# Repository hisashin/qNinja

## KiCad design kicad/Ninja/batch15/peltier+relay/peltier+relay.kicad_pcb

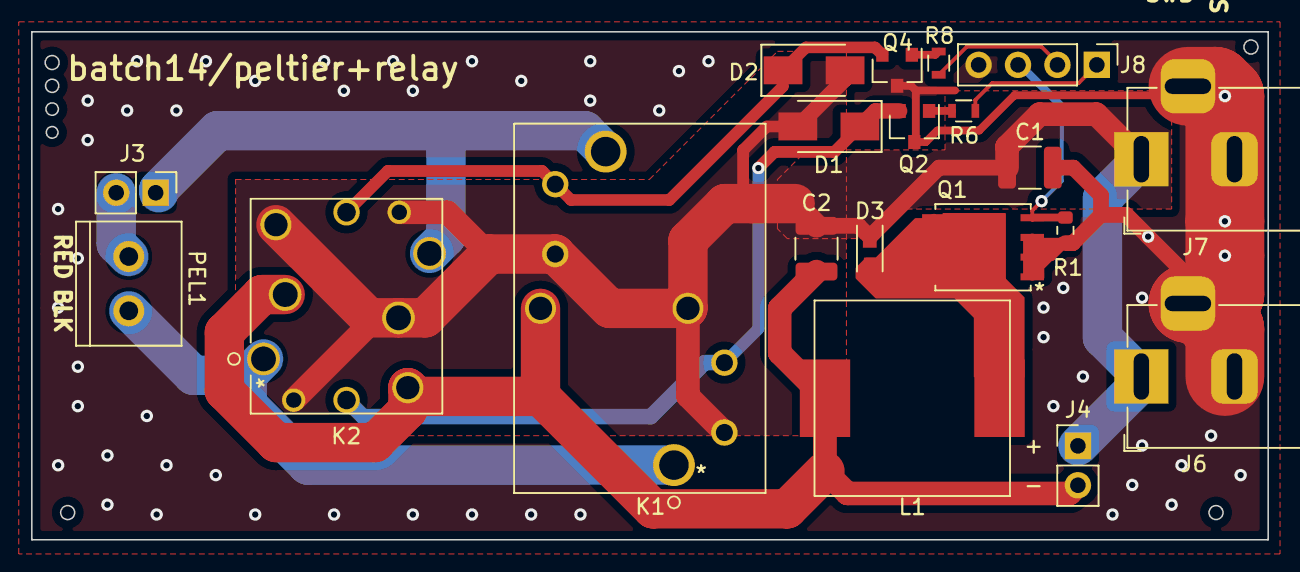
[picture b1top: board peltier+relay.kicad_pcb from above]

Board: 2 copper layers, 79.7 x 32.7 mm, 20 parts (0 on the bottom side), 14 nets.

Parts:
C1, C2: 22uF; C_1210_3225Metric
D1, D2: DIODE; D_SMA
D3: D_Schottky; MSS1P3L-M3&slash_89A
J3, J4: Conn_01x02_Female; Pin_Header_Straight_1x02_Pitch2.54mm
J6, J7: Barrel_Jack_Switch; BarrelJack_Horizontal
J8: Conn_01x03_Male; Pin_Header_Straight_1x04_Pitch2.54mm
K1: EP2-3L3SAb
K2: EX2-2U1S
L1: SRP1265C-220M; SRP1265C
PEL1: Screw_Terminal_01x02; TB_SeeedOPL_320110028
Q1: SIRA88BDP-T1-GE3; PowerPAK_SO-8_Long
Q2, Q4: Q_NPN_BCE; SOT-23
R1: 10k; R_0603_1608Metric
R6, R8: 10k; R_0603

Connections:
12V: C1.1, C2.1, D1.2, D2.2, D3.1, J4.1, J6.1, J7.1, K1.2, K1.4, K1.6, K2.2, K2.5, K2.7, K2.9
/PEL1: D1.1, K1.3, K2.3, Q2.2
/PEL3: D2.1, K1.7, K2.8, Q4.2
/PEL_BLK: K1.1, K2.1, PEL1.2
/PEL_RED: J3.1, K1.8, K2.6
GND: C1.2, J6.2, J6.3, J7.2, J7.3, J8.4, Q1.1, Q1.2, Q1.3, Q2.3, Q4.3, R1.2
unnamed: D3.2, L1.1, Q1.5, Q1.6, Q1.7, Q1.8
unnamed: J3.2, PEL1.1
unnamed: Q2.1, R6.1
unnamed: Q4.1, R8.2
PEL_PWM: J8.3, Q1.4, R1.1
PEL_SWA: J8.1, R6.2
PEL_SWB: J8.2, R8.1
REG_OUT: C2.2, J4.2, K1.5, K2.4, K2.10, L1.2

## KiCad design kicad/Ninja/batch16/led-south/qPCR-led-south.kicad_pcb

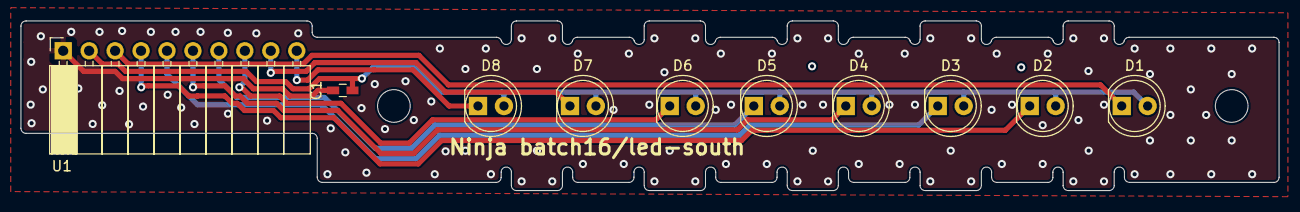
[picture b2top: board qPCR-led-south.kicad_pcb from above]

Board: 2 copper layers, 123.1 x 16.6 mm, 10 parts (0 on the bottom side), 10 nets.

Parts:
C1: C; C_0603_HandSoldering
D1, D2, D3, D4, D5, D6, D7, D8: LED; LED_D5.0mm
U1: Conn_02x05; Socket_Strip_Angled_1x10_Pitch2.54mm

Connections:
GND: C1.2, U1.1
OUT1: D1.1, U1.3
OUT2: D2.1, U1.4
OUT3: D3.1, U1.5
OUT4: D4.1, U1.6
OUT5: D5.1, U1.7
OUT6: D6.1, U1.8
OUT7: D7.1, U1.9
OUT8: D8.1, U1.10
VCC: C1.1, D1.2, D2.2, D3.2, D4.2, D5.2, D6.2, D7.2, D8.2, U1.2

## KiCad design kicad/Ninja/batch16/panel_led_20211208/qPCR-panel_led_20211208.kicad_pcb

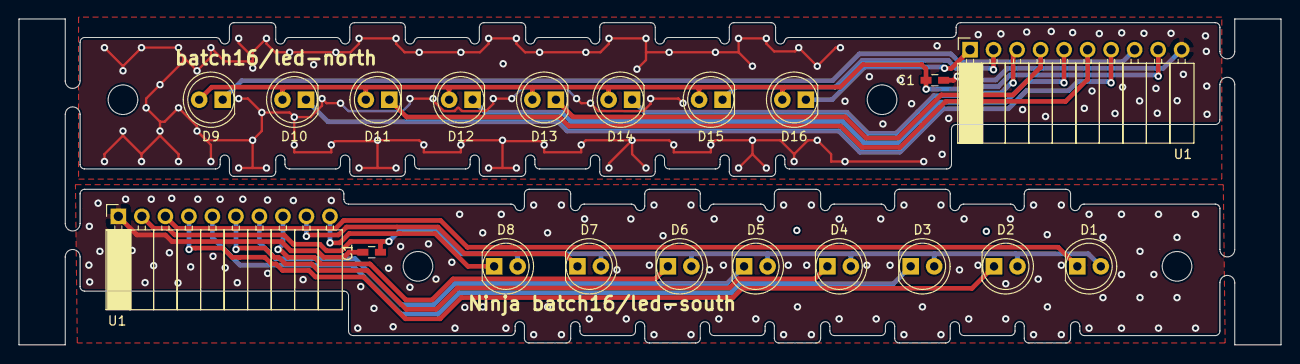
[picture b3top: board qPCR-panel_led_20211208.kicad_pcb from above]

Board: 2 copper layers, 136.3 x 35.2 mm, 20 parts (0 on the bottom side), 18 nets.

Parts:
C1, C1#2: C; C_0603_HandSoldering
D1, D2, D3, D4, D5, D6, D7, D8, D9, D10, D11, D12, D13, D14, D15, D16: LED; LED_D5.0mm
U1, U1#2: Conn_02x05; Socket_Strip_Angled_1x10_Pitch2.54mm

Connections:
GND: C1.2, C1#2.2, U1.10, U1#2.1
OUT1: D1.1, U1#2.3
OUT2: D2.1, U1#2.4
OUT3: D3.1, U1#2.5
OUT4: D4.1, U1#2.6
OUT5: D5.1, U1#2.7
OUT6: D6.1, U1#2.8
OUT7: D7.1, U1#2.9
OUT8: D8.1, U1#2.10
OUT9: D9.1, U1.8
OUT10: D10.1, U1.7
OUT11: D11.1, U1.6
OUT12: D12.1, U1.5
OUT13: D13.1, U1.4
OUT14: D14.1, U1.3
OUT15: D15.1, U1.2
OUT16: D16.1, U1.1
VCC: C1.1, C1#2.1, D1.2, D2.2, D3.2, D4.2, D5.2, D6.2, D7.2, D8.2, D9.2, D10.2, D11.2, D12.2, D13.2, D14.2, D15.2, D16.2, U1.9, U1#2.2

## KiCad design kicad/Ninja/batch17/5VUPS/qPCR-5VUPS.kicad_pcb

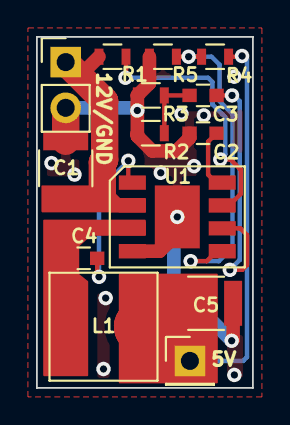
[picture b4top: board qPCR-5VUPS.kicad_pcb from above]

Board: 2 copper layers, 12.0 x 19.5 mm, 14 parts (0 on the bottom side), 10 nets.

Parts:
C1, C5: 22uF; C_1210
C2: 0.1uF; C_0603
C3, C4: 0.01uF; C_0603
J1: Conn_01x02_Male; Pin_Header_Straight_1x02_Pitch2.54mm
J2: Conn_01x01_Male; Pin_Header_Straight_1x01_Pitch2.54mm
L1: 10uH; VLS6045EX-3R3N
R1: 100k/150k; R_0603
R2, R3, R5: 10k; R_0603
R4: 47k; R_0603
U1: AP6503

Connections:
5V_UPS: C5.2, J2.1, L1.1, R4.1
12V_UPS: C1.2, J1.1, R1.1, U1.2
GND: C1.1, C2.1, C5.1, J1.2, R2.2, R3.2, R5.2, U1.4, U1.9
unnamed: C2.2, U1.8
unnamed: C3.1, R2.1, R3.1
unnamed: C3.2, U1.6
unnamed: C4.1, U1.1
unnamed: C4.2, L1.2, U1.3
unnamed: R1.2, U1.7
unnamed: R4.2, R5.1, U1.5

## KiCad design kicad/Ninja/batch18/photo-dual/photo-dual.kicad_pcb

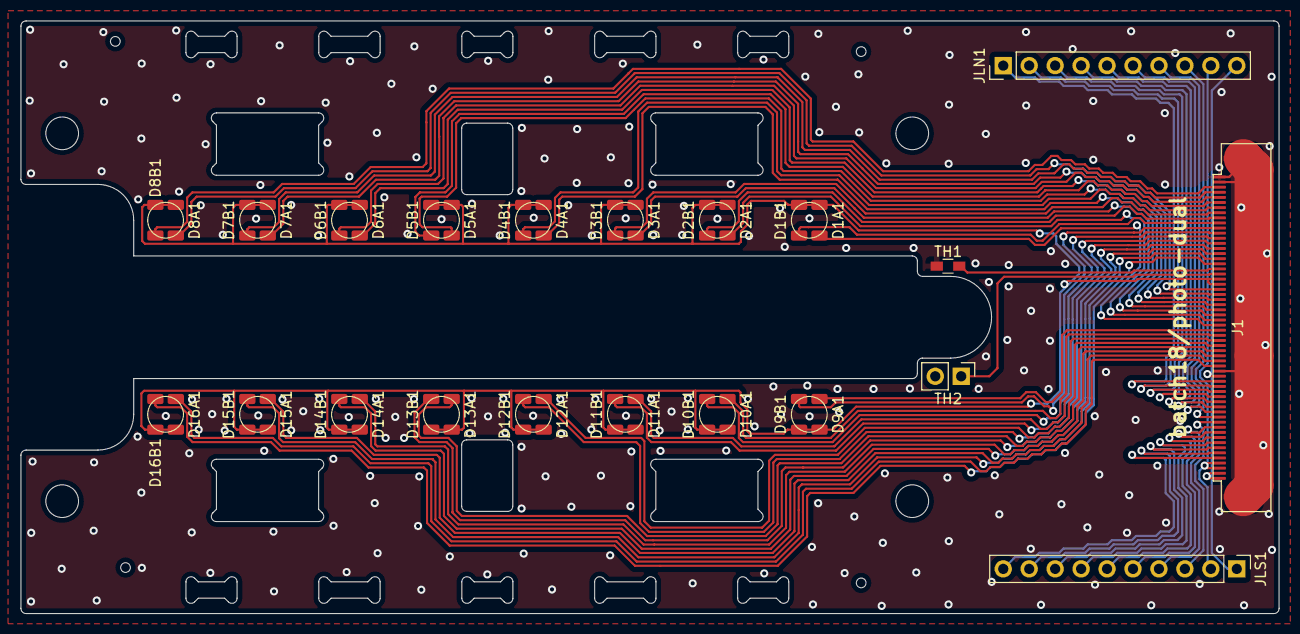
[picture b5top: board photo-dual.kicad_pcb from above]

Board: 2 copper layers, 123.1 x 58.0 mm, 37 parts (0 on the bottom side), 54 nets.

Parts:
D1A1, D1B1, D2A1, D2B1, D3A1, D3B1, D4A1, D4B1, D5A1, D5B1, D6A1, D6B1, D7A1, D7B1, D8A1, D8B1, D9A1, D9B1, D10A1, D10B1, D11A1, D11B1, D12A1, D12B1, D13A1, D13B1, D14A1, D14B1, D15A1, D15B1, D16A1, D16B1: D_Photo; D_1206_nosilk
J1: Conn_01x60_Male; FFC_60_Ali_HUISHUNFA
JLN1: Conn_01x10_Male; Pin_Header_Straight_1x10_Pitch2.54mm
JLS1: Conn_01x10_Male; Pin_Header_Straight_1x10_Pitch2.54mm
TH1: Thermistor; R_0603_HandSoldering
TH2: Thermistor; PinHeader_1x02_P2.54mm_Vertical

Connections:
/N_LED_OUT1: J1.20, JLN1.1
/N_LED_OUT2: J1.19, JLN1.2
/N_LED_OUT3: J1.18, JLN1.3
/N_LED_OUT4: J1.17, JLN1.4
/N_LED_OUT5: J1.16, JLN1.5
/N_LED_OUT6: J1.15, JLN1.6
/N_LED_OUT7: J1.14, JLN1.7
/N_LED_OUT8: J1.13, JLN1.8
/N_PD_OUT1: D1A1.2 (A), J1.31
/N_PD_OUT2: D1B1.2 (A), J1.51
/N_PD_OUT3: D2A1.2 (A), J1.32
/N_PD_OUT4: D2B1.2 (A), J1.52
/N_PD_OUT5: D3A1.2 (A), J1.33
/N_PD_OUT6: D3B1.2 (A), J1.53
/N_PD_OUT7: D4A1.2 (A), J1.34
/N_PD_OUT8: D4B1.2 (A), J1.54
/N_PD_OUT9: D5A1.2 (A), J1.35
/N_PD_OUT10: D5B1.2 (A), J1.55
/N_PD_OUT11: D6A1.2 (A), J1.36
/N_PD_OUT12: D6B1.2 (A), J1.56
/N_PD_OUT13: D7A1.2 (A), J1.37
/N_PD_OUT14: D7B1.2 (A), J1.57
/N_PD_OUT15: D8A1.2 (A), J1.38
/N_PD_OUT16: D8B1.2 (A), J1.58
/S_LED_OUT1: J1.12, JLS1.3
/S_LED_OUT2: J1.11, JLS1.4
/S_LED_OUT3: J1.10, JLS1.5
/S_LED_OUT4: J1.9, JLS1.6
/S_LED_OUT5: J1.8, JLS1.7
/S_LED_OUT6: J1.7, JLS1.8
/S_LED_OUT7: J1.6, JLS1.9
/S_LED_OUT8: J1.5, JLS1.10
/S_PD_OUT1: D9A1.2 (A), J1.30
/S_PD_OUT2: D9B1.2 (A), J1.50
/S_PD_OUT3: D10A1.2 (A), J1.29
/S_PD_OUT4: D10B1.2 (A), J1.49
/S_PD_OUT5: D11A1.2 (A), J1.28
/S_PD_OUT6: D11B1.2 (A), J1.48
/S_PD_OUT7: D12A1.2 (A), J1.27
/S_PD_OUT8: D12B1.2 (A), J1.47
/S_PD_OUT9: D13A1.2 (A), J1.26
/S_PD_OUT10: D13B1.2 (A), J1.46
/S_PD_OUT11: D14A1.2 (A), J1.25
/S_PD_OUT12: D14B1.2 (A), J1.45
/S_PD_OUT13: D15A1.2 (A), J1.24
/S_PD_OUT14: D15B1.2 (A), J1.44
/S_PD_OUT15: D16A1.2 (A), J1.23
/S_PD_OUT16: D16B1.2 (A), J1.43
/TH1: J1.42, TH1.1
/TH2: J1.41, TH2.1
GNDA: J1.22, J1.59, J1.60, J1.G1, J1.G2, TH1.2, TH2.2
GNDL: J1.1, J1.2, J1.21, JLN1.10, JLS1.1
VCCA: D1A1.1 (K), D1B1.1 (K), D2A1.1 (K), D2B1.1 (K), D3A1.1 (K), D3B1.1 (K), D4A1.1 (K), D4B1.1 (K), D5A1.1 (K), D5B1.1 (K), D6A1.1 (K), D6B1.1 (K), D7A1.1 (K), D7B1.1 (K), D8A1.1 (K), D8B1.1 (K), D9A1.1 (K), D9B1.1 (K), D10A1.1 (K), D10B1.1 (K), D11A1.1 (K), D11B1.1 (K), D12A1.1 (K), D12B1.1 (K), D13A1.1 (K), D13B1.1 (K), D14A1.1 (K), D14B1.1 (K), D15A1.1 (K), D15B1.1 (K), D16A1.1 (K), D16B1.1 (K), J1.39, J1.40
VCCL: J1.3, J1.4, JLN1.9, JLS1.2

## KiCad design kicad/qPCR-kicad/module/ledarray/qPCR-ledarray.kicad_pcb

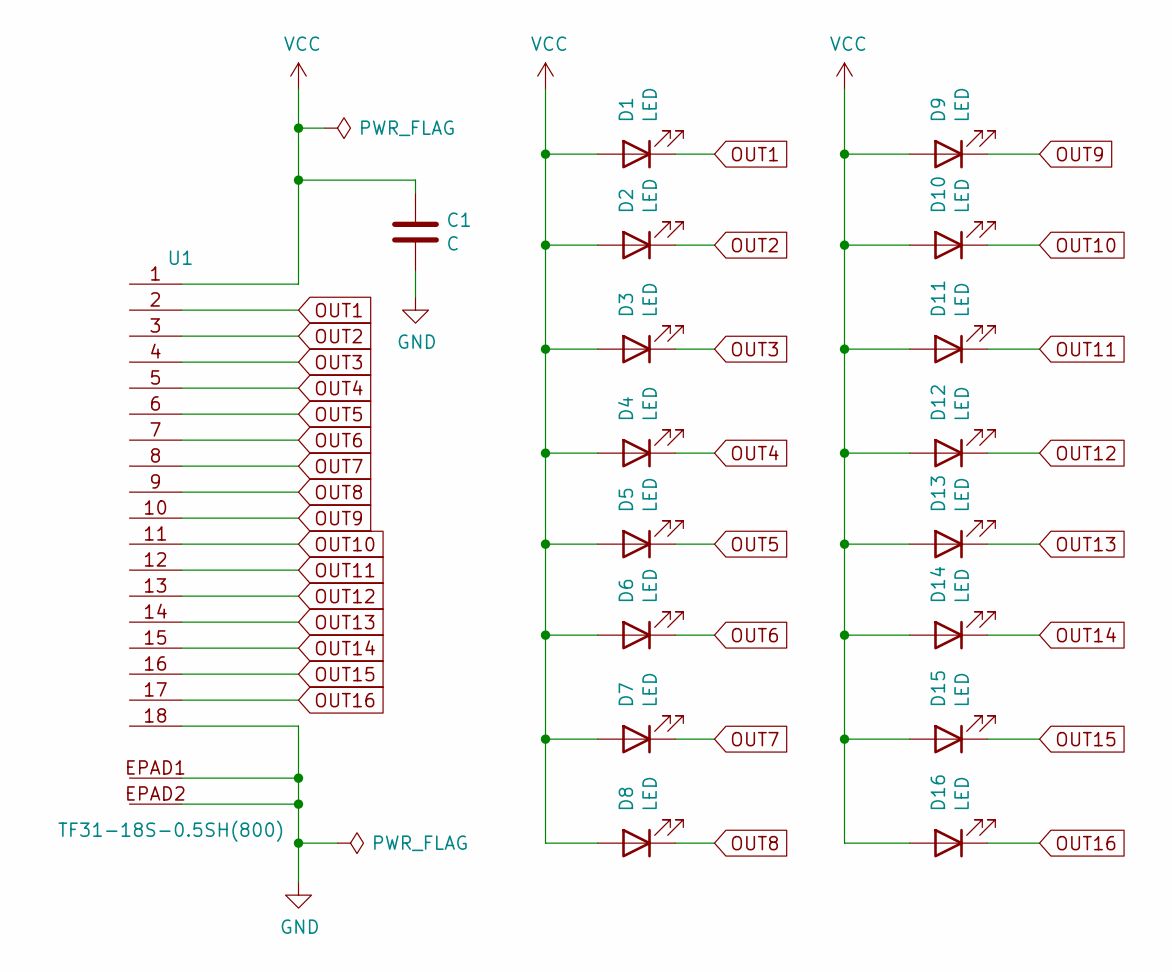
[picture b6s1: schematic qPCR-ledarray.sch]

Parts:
C1: C; C_1206_HandSoldering
D1, D2, D3, D4, D5, D6, D7, D8, D9, D10, D11, D12, D13, D14, D15, D16: LED; LED_D5.0mm
U1: TF31-18S-0.5SH(800)

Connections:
GND: C1.2, U1.18, U1.EPAD1, U1.EPAD2; also elsewhere on the board
OUT1: D1.1 (K), U1.2; also elsewhere on the board
OUT2: D2.1 (K), U1.3; also elsewhere on the board
OUT3: D3.1 (K), U1.4; also elsewhere on the board
OUT4: D4.1 (K), U1.5; also elsewhere on the board
OUT5: D5.1 (K), U1.6; also elsewhere on the board
OUT6: D6.1 (K), U1.7; also elsewhere on the board
OUT7: D7.1 (K), U1.8; also elsewhere on the board
OUT8: D8.1 (K), U1.9; also elsewhere on the board
OUT9: D9.1 (K), U1.10; also elsewhere on the board
OUT10: D10.1 (K), U1.11; also elsewhere on the board
OUT11: D11.1 (K), U1.12; also elsewhere on the board
OUT12: D12.1 (K), U1.13; also elsewhere on the board
OUT13: D13.1 (K), U1.14; also elsewhere on the board
OUT14: D14.1 (K), U1.15; also elsewhere on the board
OUT15: D15.1 (K), U1.16; also elsewhere on the board
OUT16: D16.1 (K), U1.17; also elsewhere on the board
VCC: C1.1, D1.2 (A), D2.2 (A), D3.2 (A), D4.2 (A), D5.2 (A), D6.2 (A), D7.2 (A), D8.2 (A), D9.2 (A), D10.2 (A), D11.2 (A), D12.2 (A), D13.2 (A), D14.2 (A), D15.2 (A), D16.2 (A), U1.1; also elsewhere on the board

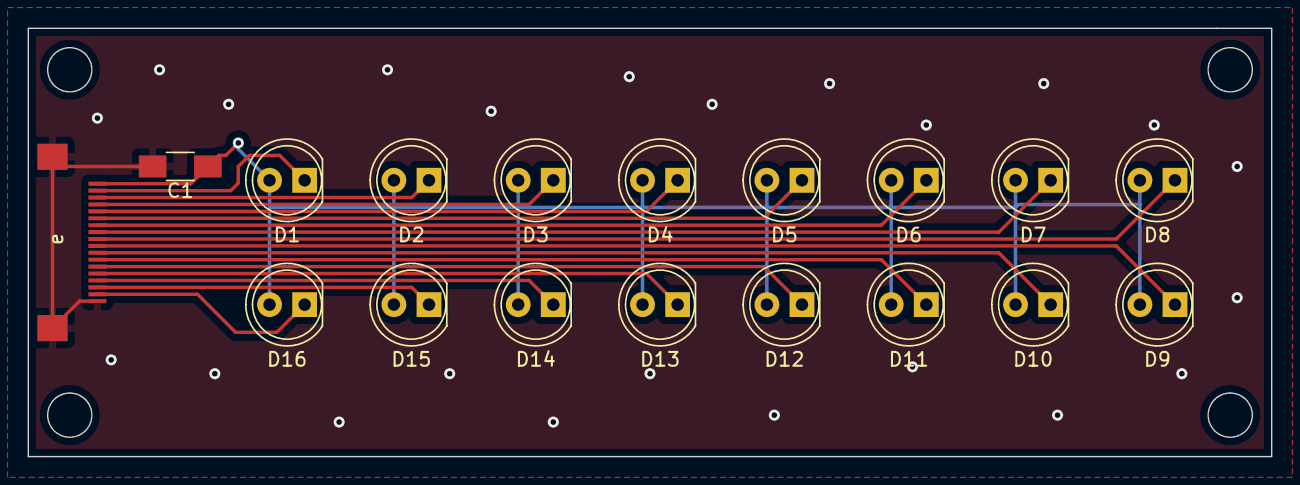
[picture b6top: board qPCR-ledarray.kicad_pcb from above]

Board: 2 copper layers, 90.0 x 31.0 mm, 18 parts (0 on the bottom side), 18 nets.

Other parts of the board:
e: TF31-18S-0.5SH(800)

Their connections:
GND: e.18, e.EPAD1, e.EPAD2; also elsewhere on the board
OUT1: e.2; also elsewhere on the board
OUT2: e.3; also elsewhere on the board
OUT3: e.4; also elsewhere on the board
OUT4: e.5; also elsewhere on the board
OUT5: e.6; also elsewhere on the board
OUT6: e.7; also elsewhere on the board
OUT7: e.8; also elsewhere on the board
OUT8: e.9; also elsewhere on the board
OUT9: e.10; also elsewhere on the board
OUT10: e.11; also elsewhere on the board
OUT11: e.12; also elsewhere on the board
OUT12: e.13; also elsewhere on the board
OUT13: e.14; also elsewhere on the board
OUT14: e.15; also elsewhere on the board
OUT15: e.16; also elsewhere on the board
OUT16: e.17; also elsewhere on the board
VCC: e.1; also elsewhere on the board

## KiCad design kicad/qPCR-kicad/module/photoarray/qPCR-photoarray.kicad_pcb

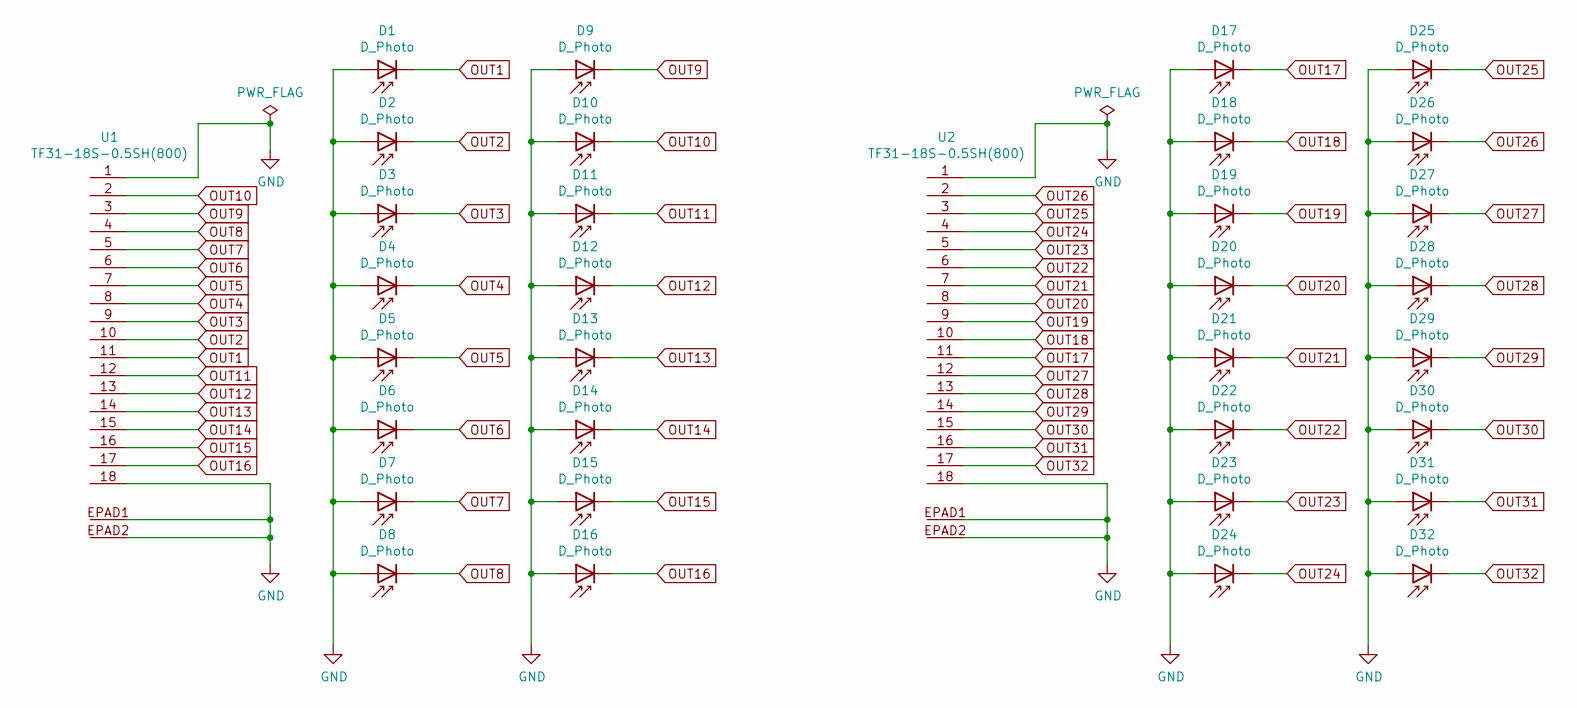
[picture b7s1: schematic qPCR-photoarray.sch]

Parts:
D1, D2, D3, D4, D5, D6, D7, D8, D9, D10, D11, D12, D13, D14, D15, D16: D_Photo; D_1206
D17, D18, D19, D20, D21, D22, D23, D24, D25, D26, D27, D28, D29, D30, D31, D32: D_Photo; D_0805
U1, U2: TF31-18S-0.5SH(800)

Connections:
GND: D1.2 (A), D2.2 (A), D3.2 (A), D4.2 (A), D5.2 (A), D6.2 (A), D7.2 (A), D8.2 (A), D9.2 (A), D10.2 (A), D11.2 (A), D12.2 (A), D13.2 (A), D14.2 (A), D15.2 (A), D16.2 (A), D17.2 (A), D18.2 (A), D19.2 (A), D20.2 (A), D21.2 (A), D22.2 (A), D23.2 (A), D24.2 (A), D25.2 (A), D26.2 (A), D27.2 (A), D28.2 (A), D29.2 (A), D30.2 (A), D31.2 (A), D32.2 (A), U1.1, U1.18, U1.EPAD1, U1.EPAD2, U2.1, U2.18, U2.EPAD1, U2.EPAD2
OUT1: D1.1 (K), U1.11
OUT2: D2.1 (K), U1.10
OUT3: D3.1 (K), U1.9
OUT4: D4.1 (K), U1.8
OUT5: D5.1 (K), U1.7
OUT6: D6.1 (K), U1.6
OUT7: D7.1 (K), U1.5
OUT8: D8.1 (K), U1.4
OUT9: D9.1 (K), U1.3
OUT10: D10.1 (K), U1.2
OUT11: D11.1 (K), U1.12
OUT12: D12.1 (K), U1.13
OUT13: D13.1 (K), U1.14
OUT14: D14.1 (K), U1.15
OUT15: D15.1 (K), U1.16
OUT16: D16.1 (K), U1.17
OUT17: D17.1 (K), U2.11
OUT18: D18.1 (K), U2.10
OUT19: D19.1 (K), U2.9
OUT20: D20.1 (K), U2.8
OUT21: D21.1 (K), U2.7
OUT22: D22.1 (K), U2.6
OUT23: D23.1 (K), U2.5
OUT24: D24.1 (K), U2.4
OUT25: D25.1 (K), U2.3
OUT26: D26.1 (K), U2.2
OUT27: D27.1 (K), U2.12
OUT28: D28.1 (K), U2.13
OUT29: D29.1 (K), U2.14
OUT30: D30.1 (K), U2.15
OUT31: D31.1 (K), U2.16
OUT32: D32.1 (K), U2.17

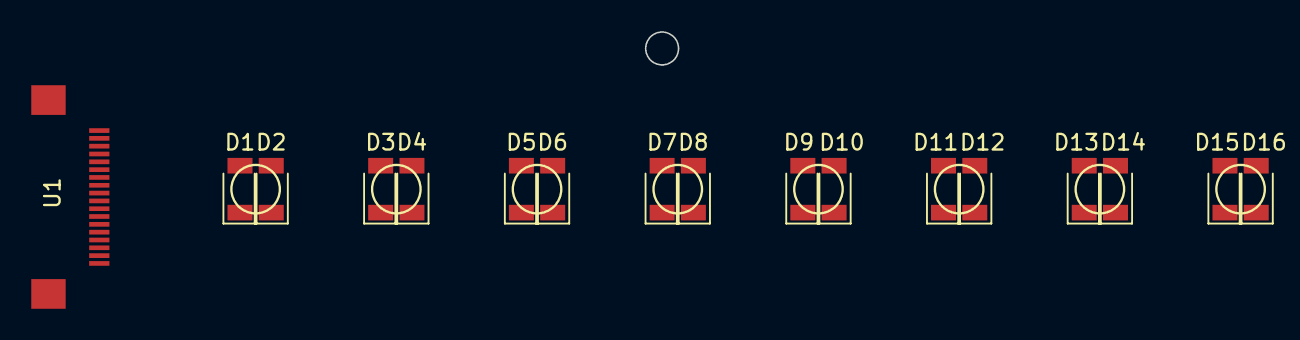
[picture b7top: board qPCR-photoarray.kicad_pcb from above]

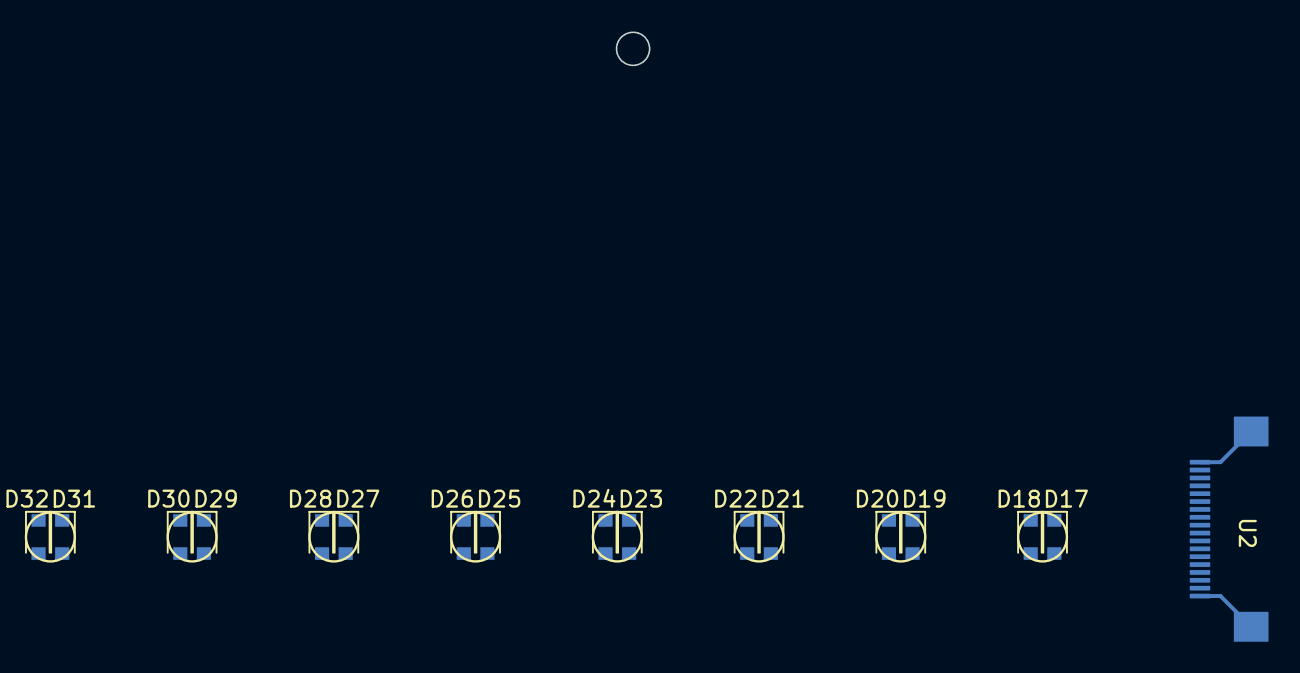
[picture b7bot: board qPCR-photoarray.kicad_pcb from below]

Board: 2 copper layers, 34 parts (17 on the bottom side), 33 nets.

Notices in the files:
parts and their libraries:
Copyright 2021 Accelerated Designs. All rights reserved.
